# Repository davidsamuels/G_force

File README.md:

# G_force : repository of my passion project involving microcontrollers and motorsports

## hardware chart
prototype | status | notes | picture |
---|---|---| --- | 
version 0 | done | proof of concept in C with arduino dev board | 
version 1 | done | directionality and RGB in C with arduino dev board |
version 2 | done | switching to rasperby pi rp2040  dev board due to chip shortage. Code still being ported. Partial PCB done with manufacturing files and tested |     
version 3| IP | custom PCB with all components. Switching to Esp32 ecosystem due to wifi/BT |  

*prototype version 1 hardware shown below*
---

Acceleration high point of view.

https://user-images.githubusercontent.com/15238565/163253612-991ed954-f6e4-438f-9013-d2a51dcb510f.mp4

Acceleration gauge cluster point of view.
**note colors are not getting picked up by the gopro well**. Look at the 12 and 6 positions on display to see readout.

https://user-images.githubusercontent.com/15238565/163262918-7c1ad50d-a557-4db1-85e5-fd604fd82128.mp4

Demo code showing the crosshair display.

Still image of crosshair display

PCB layout screenshot.

3D render of prototype hardware v2

3D render of prototype hardware v3

Back side view

Schematic v3

Layout v3

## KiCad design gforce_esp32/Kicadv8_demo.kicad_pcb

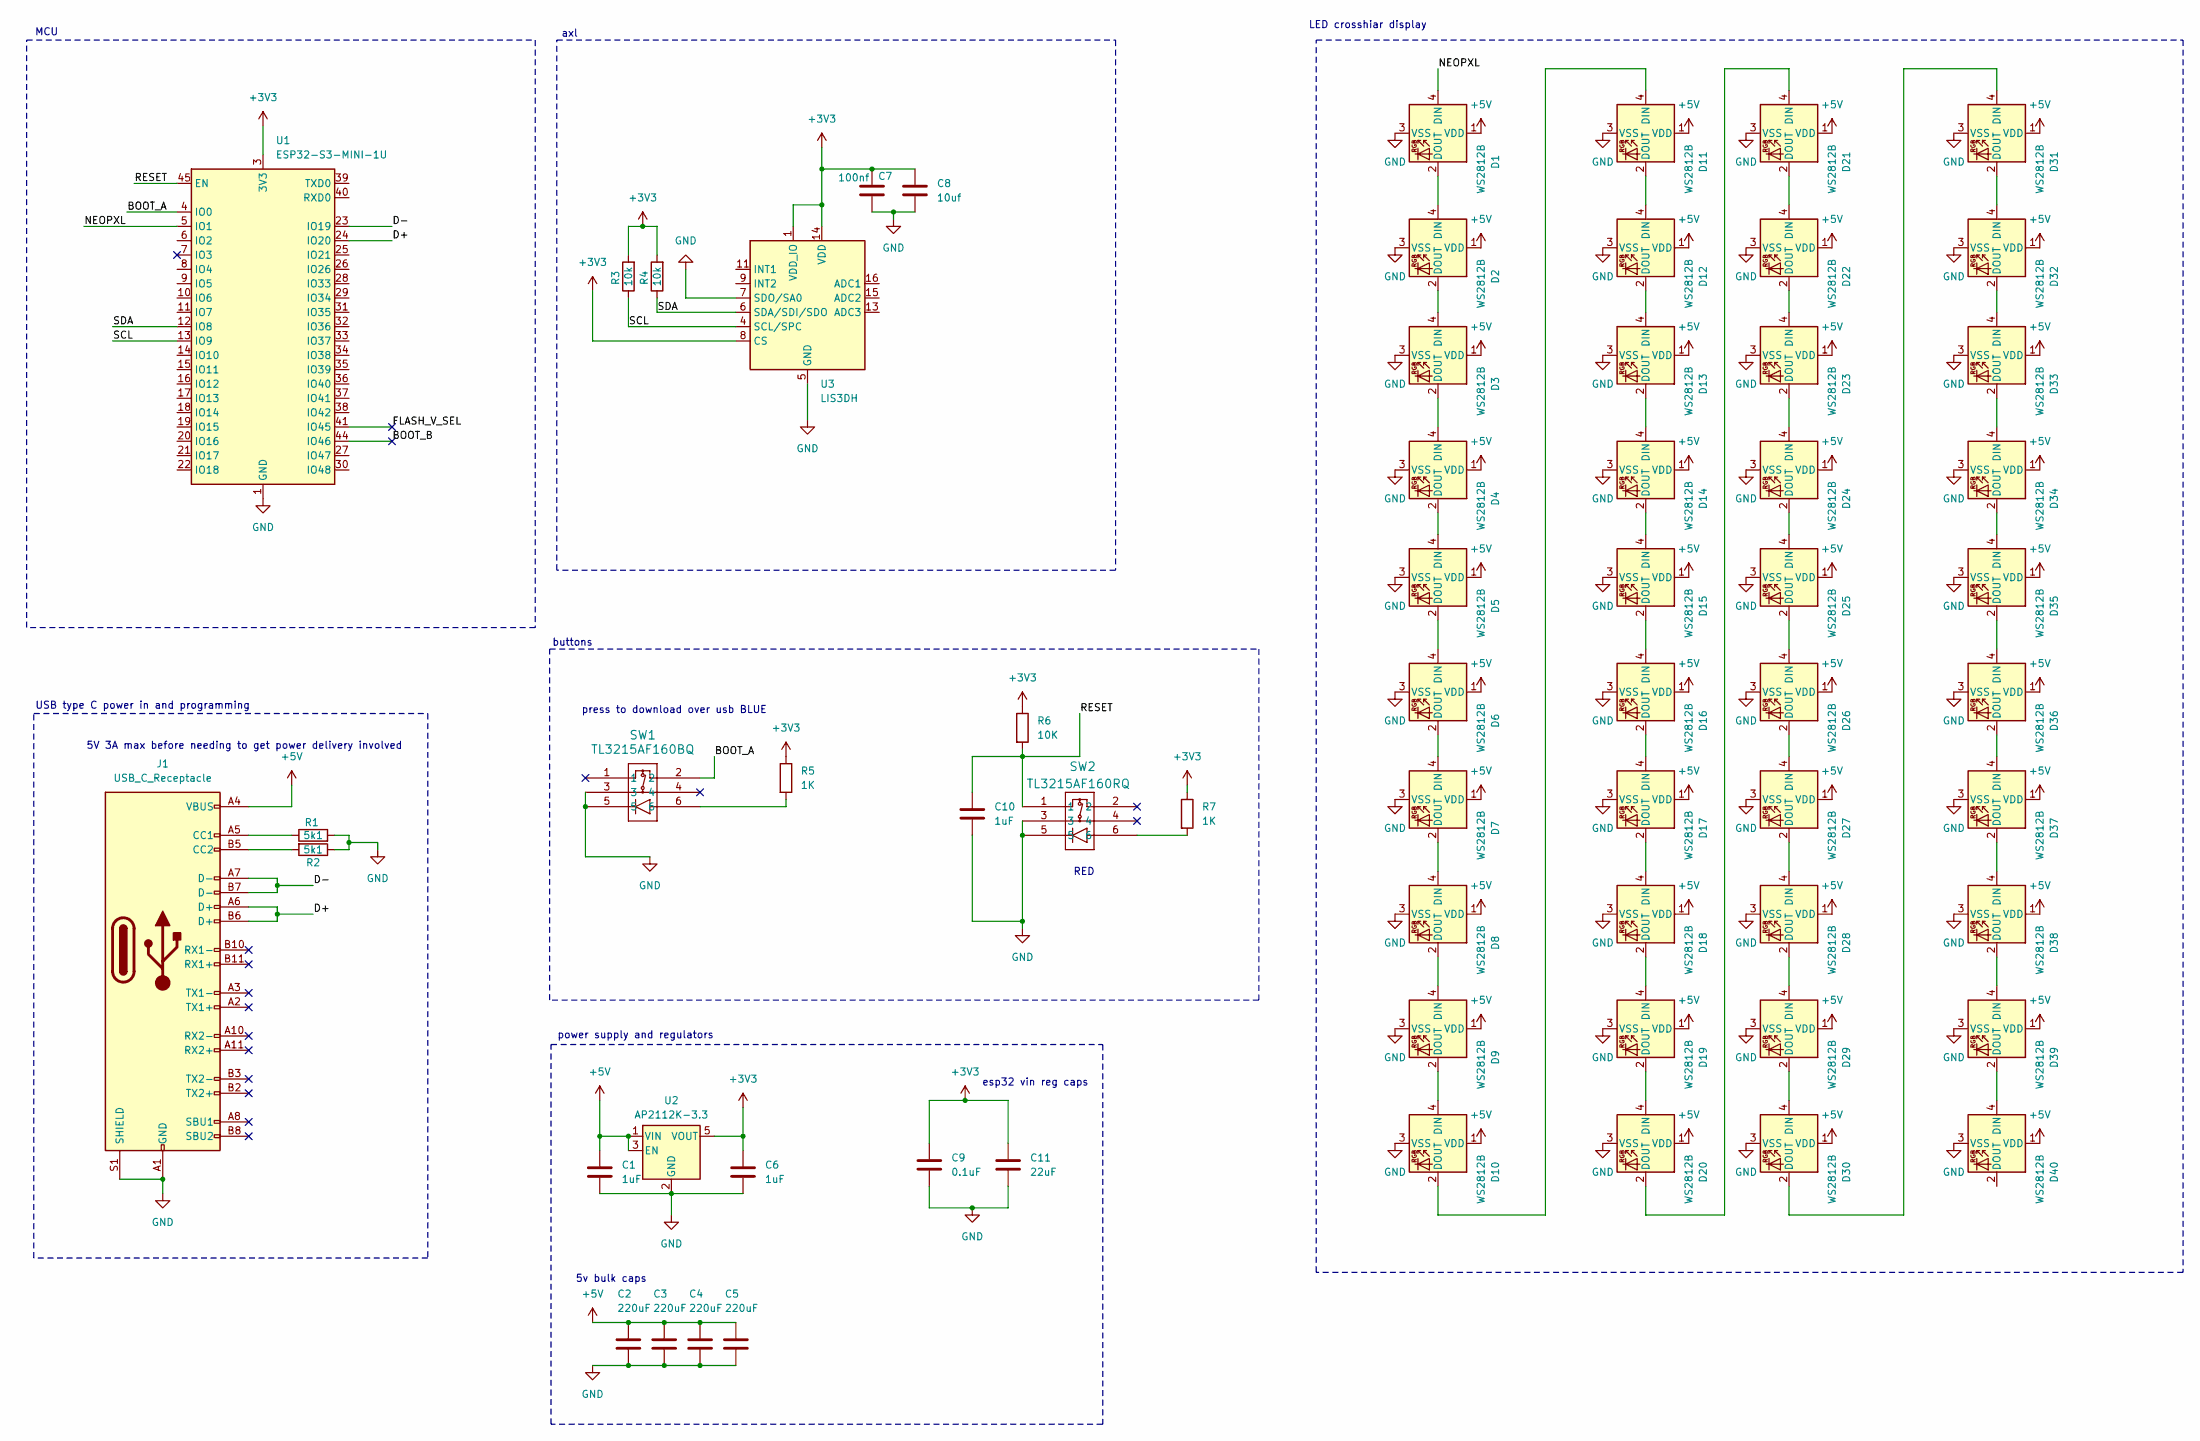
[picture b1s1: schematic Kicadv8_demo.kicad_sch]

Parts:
C1, C6, C10: 1uF; C_0603_1608Metric
C2, C3, C4, C5: 220uF; C_1206_3216Metric
C7: 100nf; C_0402_1005Metric
C8: 10uf; C_0805_2012Metric
C9: 0.1uF; C_0603_1608Metric
C11: 22uF; C_0603_1608Metric
D1, D2, D3, D4, D5, D6, D7, D8, D9, D10, D11, D12, D13, D14, D15, D16, D17, D18, D19, D20, D21, D22, D23, D24, D25, D26, D27, D28, D29, D30, D31, D32, D33, D34, D35, D36, D37, D38, D39, D40: WS2812B; LED_WS2812B_PLCC4_5.0x5.0mm_P3.2mm; LCSC Part Number C2761795
J1: USB_C_Receptacle; USB_C_Receptacle_Molex_105450-0101
R1, R2: 5k1; R_0603_1608Metric
R3, R4: 10k; R_0603_1608Metric
R5, R7: 1K; R_0603_1608Metric
R6: 10K; R_0603_1608Metric
SW1: TL3215AF160BQ; TL3215AF160BQ_EWI
SW2: TL3215AF160RQ; TL3215AF160BQ_EWI
U1: ESP32-S3-MINI-1U; ESP32-S2-MINI-1U
U2: AP2112K-3.3; SOT-23-5
U3: LIS3DH; LGA-16_3x3mm_P0.5mm_LayoutBorder3x5y

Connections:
+3V3: C6.1, C7.1, C8.1, C9.1, C11.1, R3.2, R4.2, R5.1, R6.1, R7.1, U1.3 (3V3), U2.5 (VOUT), U3.1 (VDD_IO), U3.8 (CS), U3.14 (VDD)
+5V: C1.1, C2.1, C3.1, C4.1, C5.1, D1.1 (VDD), D2.1 (VDD), D3.1 (VDD), D4.1 (VDD), D5.1 (VDD), D6.1 (VDD), D7.1 (VDD), D8.1 (VDD), D9.1 (VDD), D10.1 (VDD), D11.1 (VDD), D12.1 (VDD), D13.1 (VDD), D14.1 (VDD), D15.1 (VDD), D16.1 (VDD), D17.1 (VDD), D18.1 (VDD), D19.1 (VDD), D20.1 (VDD), D21.1 (VDD), D22.1 (VDD), D23.1 (VDD), D24.1 (VDD), D25.1 (VDD), D26.1 (VDD), D27.1 (VDD), D28.1 (VDD), D29.1 (VDD), D30.1 (VDD), D31.1 (VDD), D32.1 (VDD), D33.1 (VDD), D34.1 (VDD), D35.1 (VDD), D36.1 (VDD), D37.1 (VDD), D38.1 (VDD), D39.1 (VDD), D40.1 (VDD), J1.A4 (VBUS), J1.A9 (VBUS), J1.B4 (VBUS), J1.B9 (VBUS), U2.1 (VIN), U2.3 (EN)
/BOOT_A: SW1.2, U1.4 (IO0)
/BOOT_B: U1.44 (IO46)
/D+: J1.A6 (D+), J1.B6 (D+), U1.24 (IO20)
/D-: J1.A7 (D-), J1.B7 (D-), U1.23 (IO19)
/FLASH_V_SEL: U1.41 (IO45)
/NEOPXL: D1.4 (DIN), U1.5 (IO1)
/RESET: C10.1, R6.2, SW2.1, U1.45 (EN)
/SCL: R3.1, U1.13 (IO9), U3.4 (SCL/SPC)
/SDA: R4.1, U1.12 (IO8), U3.6 (SDA/SDI/SDO)
GND: C1.2, C2.2, C3.2, C4.2, C5.2, C6.2, C7.2, C8.2, C9.2, C10.2, C11.2, D1.3 (VSS), D2.3 (VSS), D3.3 (VSS), D4.3 (VSS), D5.3 (VSS), D6.3 (VSS), D7.3 (VSS), D8.3 (VSS), D9.3 (VSS), D10.3 (VSS), D11.3 (VSS), D12.3 (VSS), D13.3 (VSS), D14.3 (VSS), D15.3 (VSS), D16.3 (VSS), D17.3 (VSS), D18.3 (VSS), D19.3 (VSS), D20.3 (VSS), D21.3 (VSS), D22.3 (VSS), D23.3 (VSS), D24.3 (VSS), D25.3 (VSS), D26.3 (VSS), D27.3 (VSS), D28.3 (VSS), D29.3 (VSS), D30.3 (VSS), D31.3 (VSS), D32.3 (VSS), D33.3 (VSS), D34.3 (VSS), D35.3 (VSS), D36.3 (VSS), D37.3 (VSS), D38.3 (VSS), D39.3 (VSS), D40.3 (VSS), J1.A1 (GND), J1.A12 (GND), J1.B1 (GND), J1.B12 (GND), J1.S1 (SHIELD), R1.2, R2.1, SW1.3, SW1.5, SW2.3, SW2.5, U1.1 (GND), U1.2 (GND), U1.42 (GND), U1.43 (GND), U1.46 (GND), U1.47 (GND), U1.48 (GND), U1.49 (GND), U1.50 (GND), U1.51 (GND), U1.52 (GND), U1.53 (GND), U1.54 (GND), U1.55 (GND), U1.56 (GND), U1.57 (GND), U1.58 (GND), U1.59 (GND), U1.60 (GND), U1.61 (GND), U1.62 (GND), U1.63 (GND), U1.64 (GND), U1.65 (GND), U2.2 (GND), U3.5 (GND), U3.7 (SDO/SA0), U3.10 (GND), U3.12 (GND)
unnamed: D1.2 (DOUT), D2.4 (DIN)
unnamed: D2.2 (DOUT), D3.4 (DIN)
unnamed: D3.2 (DOUT), D4.4 (DIN)
unnamed: D4.2 (DOUT), D5.4 (DIN)
unnamed: D5.2 (DOUT), D6.4 (DIN)
unnamed: D6.2 (DOUT), D7.4 (DIN)
unnamed: D7.2 (DOUT), D8.4 (DIN)
unnamed: D8.2 (DOUT), D9.4 (DIN)
unnamed: D9.2 (DOUT), D10.4 (DIN)
unnamed: D10.2 (DOUT), D11.4 (DIN)
unnamed: D11.2 (DOUT), D12.4 (DIN)
unnamed: D12.2 (DOUT), D13.4 (DIN)
unnamed: D13.2 (DOUT), D14.4 (DIN)
unnamed: D14.2 (DOUT), D15.4 (DIN)
unnamed: D15.2 (DOUT), D16.4 (DIN)
unnamed: D16.2 (DOUT), D17.4 (DIN)
unnamed: D17.2 (DOUT), D18.4 (DIN)
unnamed: D18.2 (DOUT), D19.4 (DIN)
unnamed: D19.2 (DOUT), D20.4 (DIN)
unnamed: D20.2 (DOUT), D21.4 (DIN)
unnamed: D21.2 (DOUT), D22.4 (DIN)
unnamed: D22.2 (DOUT), D23.4 (DIN)
unnamed: D23.2 (DOUT), D24.4 (DIN)
unnamed: D24.2 (DOUT), D25.4 (DIN)
unnamed: D25.2 (DOUT), D26.4 (DIN)
unnamed: D26.2 (DOUT), D27.4 (DIN)
unnamed: D27.2 (DOUT), D28.4 (DIN)
unnamed: D28.2 (DOUT), D29.4 (DIN)
unnamed: D29.2 (DOUT), D30.4 (DIN)
unnamed: D30.2 (DOUT), D31.4 (DIN)
unnamed: D31.2 (DOUT), D32.4 (DIN)
unnamed: D32.2 (DOUT), D33.4 (DIN)
unnamed: D33.2 (DOUT), D34.4 (DIN)
unnamed: D34.2 (DOUT), D35.4 (DIN)
unnamed: D35.2 (DOUT), D36.4 (DIN)
unnamed: D36.2 (DOUT), D37.4 (DIN)
unnamed: D37.2 (DOUT), D38.4 (DIN)
unnamed: D38.2 (DOUT), D39.4 (DIN)
unnamed: D39.2 (DOUT), D40.4 (DIN)
unnamed: J1.A5 (CC1), R1.1
unnamed: J1.B5 (CC2), R2.2
unnamed: R5.2, SW1.6
unnamed: R7.2, SW2.6

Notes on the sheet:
5v bulk caps
5V 3A max before needing to get power delivery involved
RED
power supply and regulators
axl
MCU
esp32 vin reg caps
LED crosshiar display
buttons
USB type C power in and programming
press to download over usb BLUE

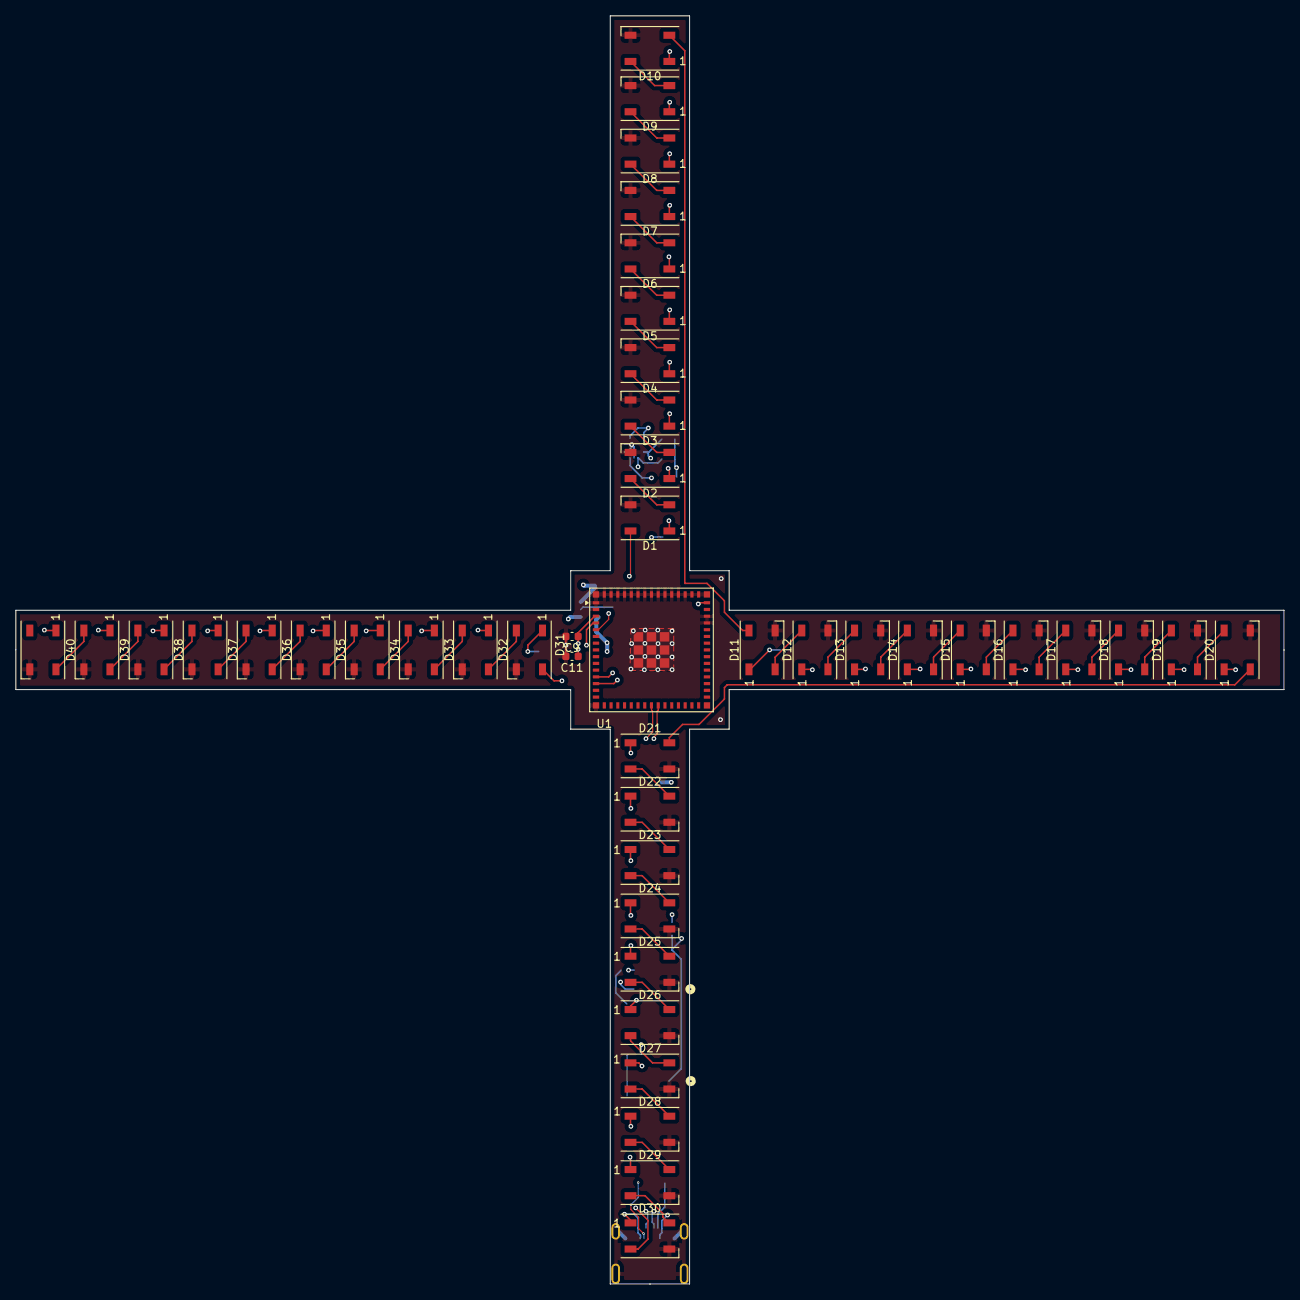
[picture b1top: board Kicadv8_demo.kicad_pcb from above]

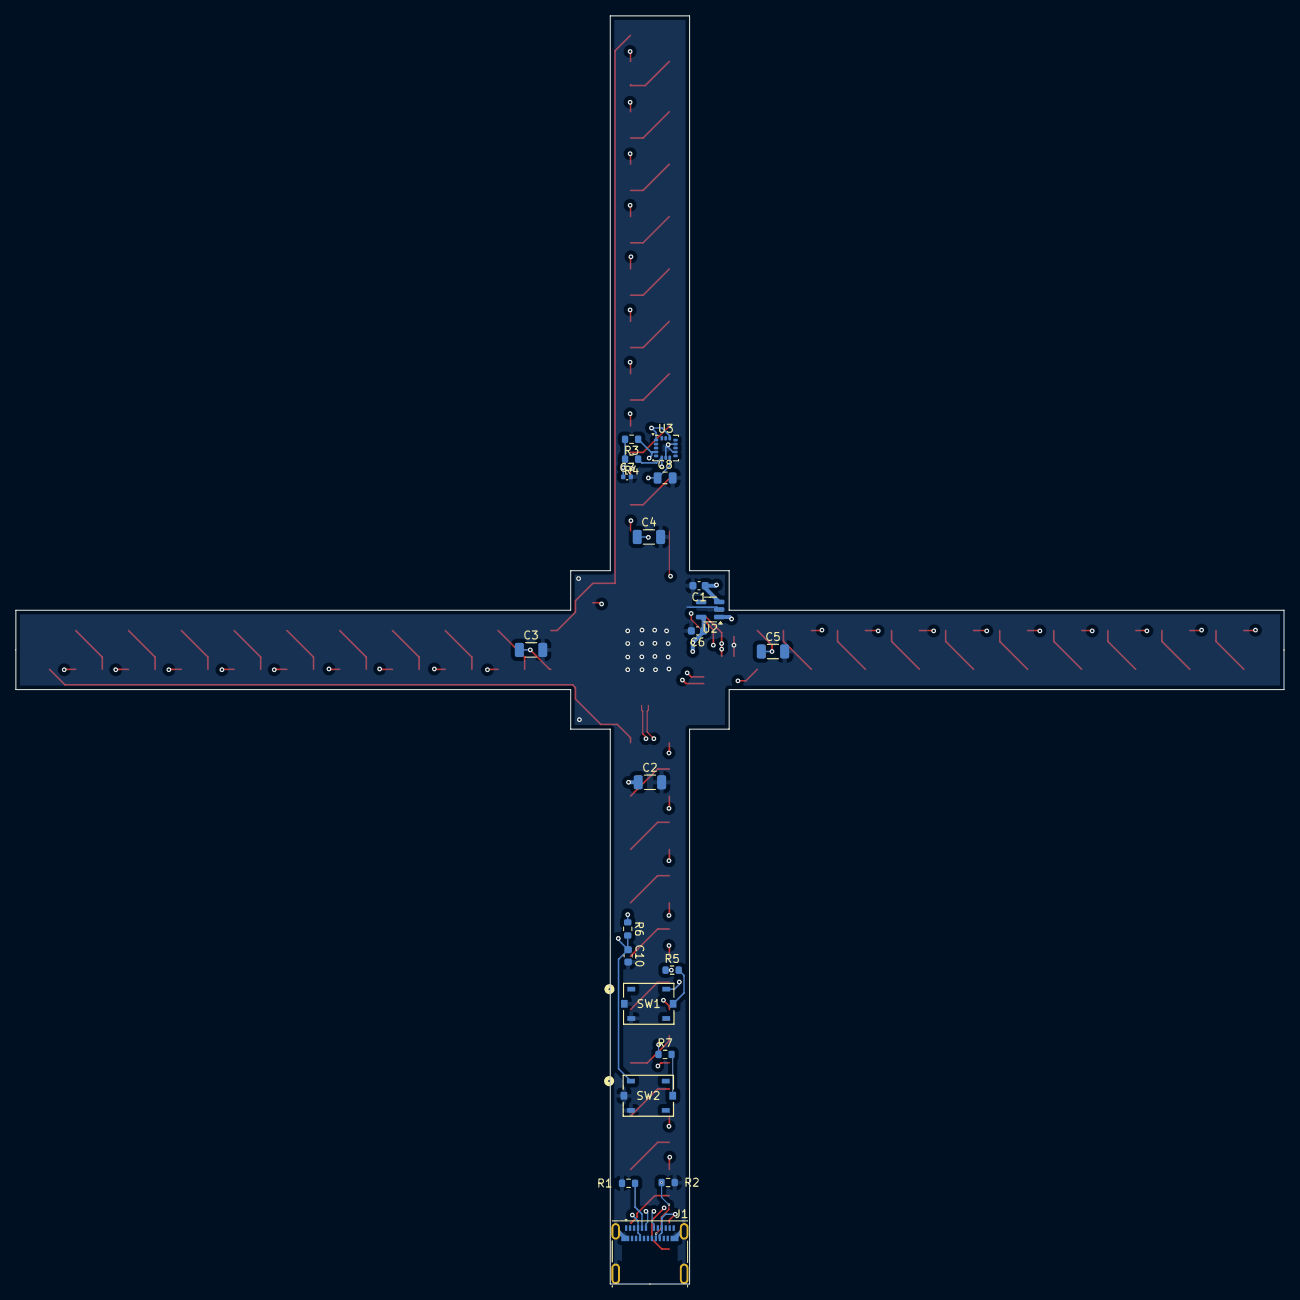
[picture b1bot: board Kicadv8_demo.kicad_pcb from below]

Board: 8 copper layers, 160.0 x 160.0 mm, 64 parts (21 on the bottom side), 53 nets.

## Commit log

2022-04-01 documents
2022-04-13 added video from hardware v2
2022-04-13 adding pcb and code files
2022-04-13 additional video
2022-04-14 added pic of pcb layout
2022-04-17 added info about each picture
2022-05-15 added table
2024-03-24 adding next version of gforce files
    kicad 8 pcb, switching to esp32 mcu
2024-03-24 gforce_esp32 is newest
    added 3d footprint of mcu
2024-03-25 usb diff pair needs updated
2024-03-25 Update README.md
    added images of v3
2024-03-25 layout placing parts
    lined up leds
2024-03-26 SCHEMATIC LEDS MAPPED. FAB NOTES ADDED
2024-03-27 some net pours and routing
2024-03-27 most important traces started to route
2024-03-28 all routing done
